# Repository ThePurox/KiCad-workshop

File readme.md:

# KiCad Workshop

- Create Project
- Install marbastlib https://github.com/ebastler/marbastlib

## Schematic

- mouse select from left, everything that is completely in selection area is included in selection
- mouse select from right, everything that touches selection are included in selection
- `a` place part
- `w` add wire
- `r` rotate
- `m` move component
- `del` delete
- `g` grab, same as `m` but move wires with it
- `l`/`ctrl-l` add label/global-label
- `q` mark pins not connected
- `p` add power net
- `v` edit value
- `e` edit properties
- assign footprints
- `F8` update PCB from schematic

## PCB

- set custom gird, alternate between grids `alt-1`, `alt-2`
- set shove setting for traces
- `m` move
- `r` rotate, `R` rotate clockwise
- `x` lay down trace
- `v` add via (in trace command)
- `f` finish trace (in trace command)
- `u` select part of trace (in trace command), multiple presses select more
- `v` (not in trace) flip board
- `f` flip component to other side
- `d` displace (move with traces)
- `b` update fills
- `h` hide/dim other stuff
- DRC, design rule checker
- edge cut
- `alt-3` view 3d render
- add fill layer

## Additional Info

- https://www.youtube.com/watch?v=Stp5BqUI48U Kliment's PCB art for terrified beginners workshop

### useful plugins

- `interactive html BOM` for generating Interactive Bill Of Materials
- `Fabrication-toolkit`
- `KiKit` for panelization and other automatization
- `KiBuzzard` for fancy-ish Text
- `Bulk hide silkscreen designators` get rid off annoying silkscreen

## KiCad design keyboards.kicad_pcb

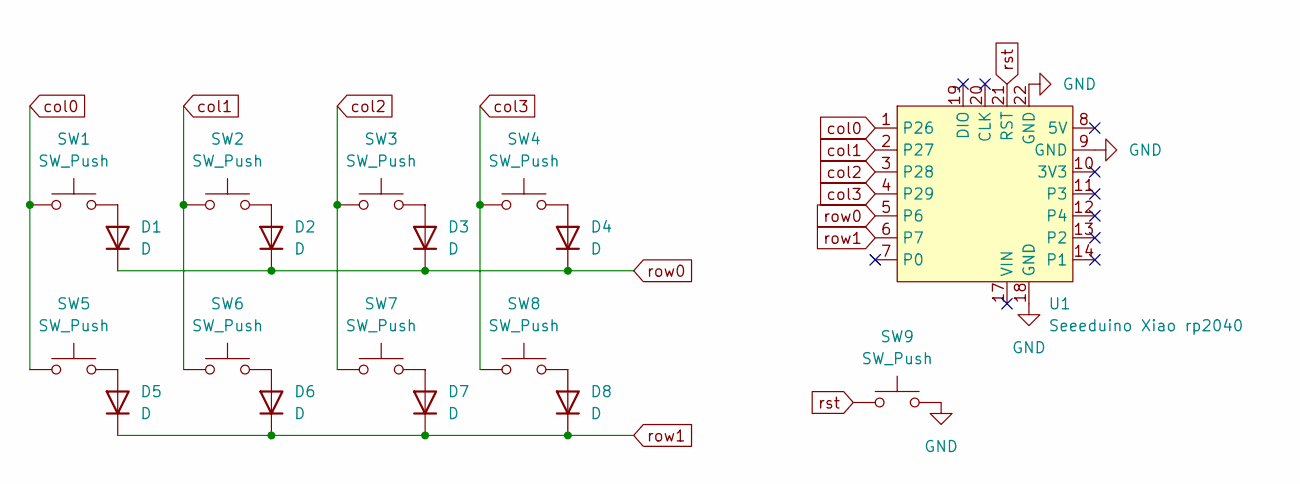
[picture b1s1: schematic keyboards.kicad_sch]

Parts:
D1, D2, D3, D4, D5, D6, D7, D8: D; D_SOD-323_HandSoldering
SW1, SW2, SW3, SW4, SW5, SW6, SW7, SW8: SW_Push; SW_MX_1u
SW9: SW_Push; SW_SPST_SKQG_WithStem
U1: Seeeduino Xiao rp2040; Xiao_rp2040_ACH

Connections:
GND: SW9.2, U1.9 (GND), U1.18 (GND), U1.22 (GND)
unnamed: D1.2 (A), SW1.2
unnamed: D2.2 (A), SW2.2
unnamed: D3.2 (A), SW3.2
unnamed: D4.2 (A), SW4.2
unnamed: D5.2 (A), SW5.2
unnamed: D6.2 (A), SW6.2
unnamed: D7.2 (A), SW7.2
unnamed: D8.2 (A), SW8.2
col0: SW1.1, SW5.1, U1.1 (P26)
col1: SW2.1, SW6.1, U1.2 (P27)
col2: SW3.1, SW7.1, U1.3 (P28)
col3: SW4.1, SW8.1, U1.4 (P29)
row0: D1.1 (K), D2.1 (K), D3.1 (K), D4.1 (K), U1.5 (P6)
row1: D5.1 (K), D6.1 (K), D7.1 (K), D8.1 (K), U1.6 (P7)
rst: SW9.1, U1.21 (RST)

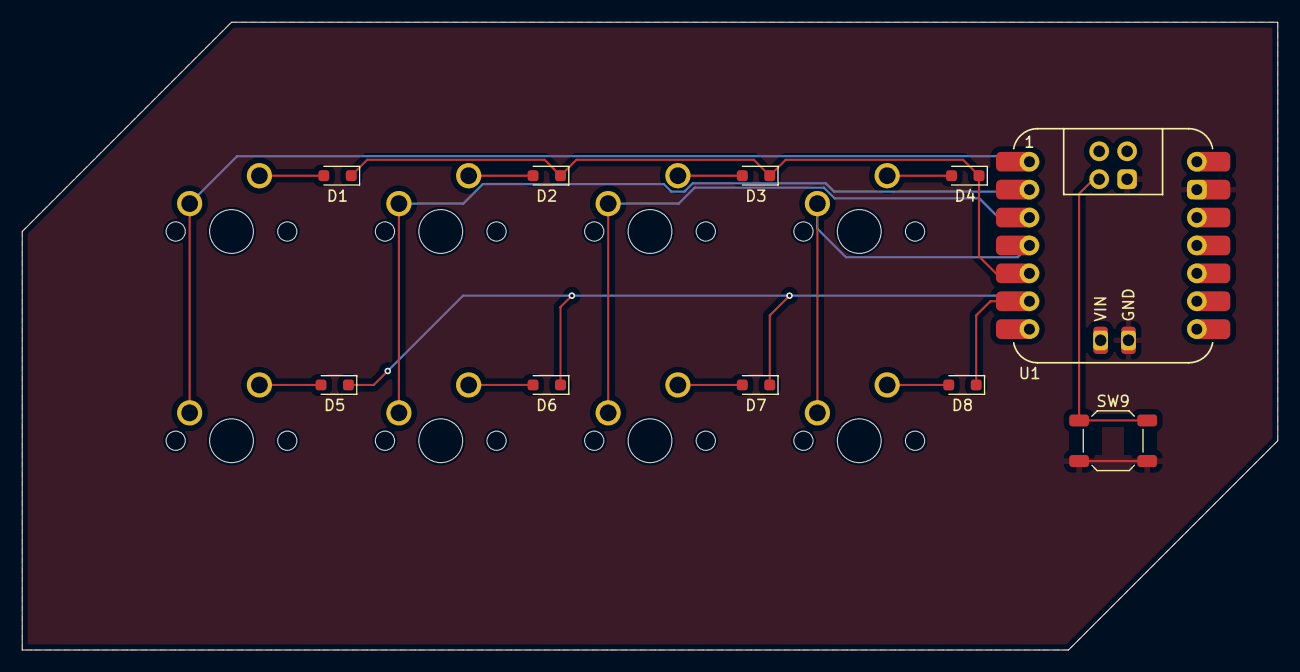
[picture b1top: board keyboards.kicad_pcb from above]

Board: 2 copper layers, 114.3 x 57.2 mm, 18 parts (0 on the bottom side), 16 nets.

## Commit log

2024-11-09 init
2024-11-09 moved notes to readme
2024-11-14 added plugins
